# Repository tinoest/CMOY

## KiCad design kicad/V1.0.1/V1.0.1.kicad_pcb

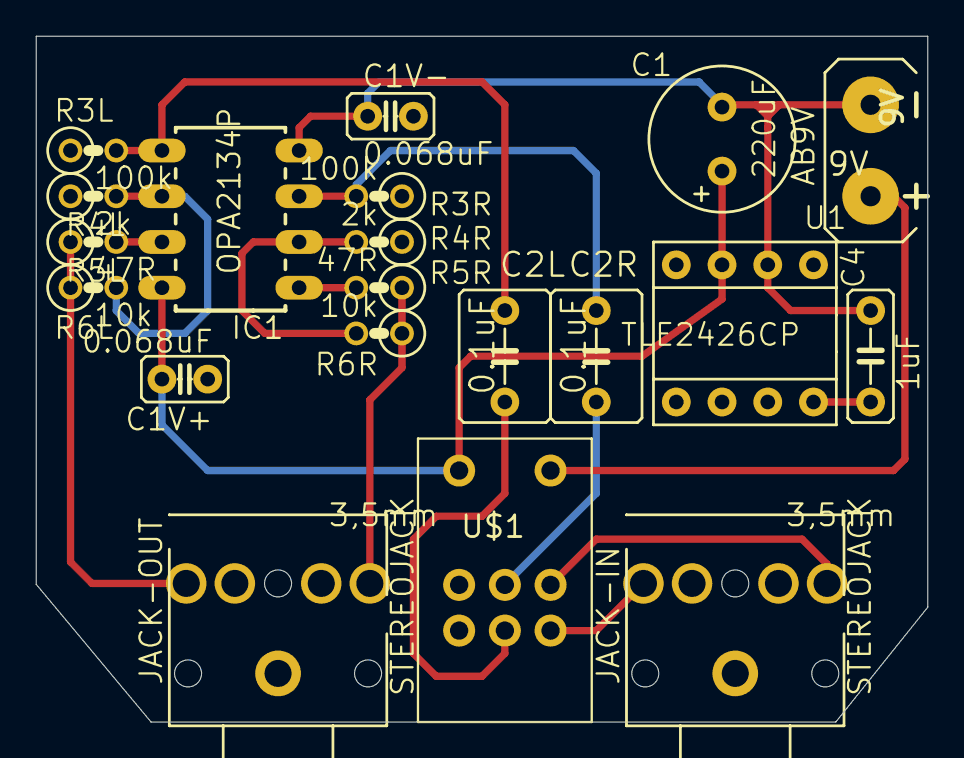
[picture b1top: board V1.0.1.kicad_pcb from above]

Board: 2 copper layers, 49.5 x 38.1 mm, 20 parts (0 on the bottom side), 17 nets.

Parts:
9V: AB9V
C1: 220uF; E3,5-8
C1V+, C1V-: 0.068uF; C2.5-2
C2L, C2R: 0.1uF; C5B5
C4: 1uF; C5B2.5
IC1: OPA2134P; DIL-8
JACK-IN: STEREOJACK; STX3100
JACK-OUT: STEREOJACK; STX3100
R3L, R3R: 100k; 0207_2V
R4L, R4R: 2k; 0207_2V
R5L, R5R: 47R; 0207_2V
R6L, R6R: 10k; 0207_2V
U1: TLE2426CP; DIP-8
U$1: ALPS_RK0971221Z0X

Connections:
GND: C1V+.1, C1V-.2, JACK-IN.1, JACK-OUT.1, R3L.1, R3R.1, R4L.1, R4R.1, U1.1, U$1.G1, U$1.G2
INPUT-L: JACK-IN.2, U$1.I1
INPUT-R: JACK-IN.5, U$1.I2
L+: C2L.1, IC1.5, R3L.2
L-: IC1.6, R4L.2, R6L.2
unnamed: 9V.+, U$1.S2
unnamed: C4.1, U1.8
OP-L: IC1.7, R5L.2
OP-R: IC1.1, R5R.2
OUTPUT-L: JACK-OUT.2, R5L.1, R6L.1
OUTPUT-R: JACK-OUT.5, R5R.1, R6R.1
R+: C2R.1, IC1.3, R3R.2
R-: IC1.2, R4R.2, R6R.2
V+: C1.+, C1V+.2, IC1.8, U1.3, U$1.S1
V-: 9V.-, C1.-, C1V-.1, C4.2, IC1.4, U1.2
VOLUME-OUT-L: C2L.2, U$1.O1
VOLUME-OUT-R: C2R.2, U$1.O2

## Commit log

2017-03-31 Adding old CMOY data files created in Eagle
    CMOY Amplifier Circuit and Board
2017-03-31 Created kicad PCB files
2017-03-31 First conversion to kicad
2017-03-31 Moved V1.0.0 to kicad
2017-03-31 Modified slightly to fix some ERC issues
2017-03-31 Moved to indvidual directories
2017-03-31 Modified PCB and Schematic so they were in sync
2017-03-31 Removed unrequired files
2017-03-31 Started to include libraries and sort out names to link to PCB
2017-03-31 Corrected Schematic errors
2017-03-31 Added cache.lib
2017-04-01 Corrected conversion errors
2017-04-01 Moved eaglecad files into eagle directory
